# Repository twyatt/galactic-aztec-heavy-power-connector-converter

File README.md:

# About

Custom board used to convert ethernet plug to 4-pin molex connector for the [Galactic Aztec Heavy] rocket. The board was designed to interface with the [Galactic Aztec Heavy Raspberry Pi Add-on: ADC] board.

Custom EagleCAD parts on this board can be found in the [SDSU Rocket Eagle Libraries].

## Wiring
The ethernet port adheres to the following [T-568B] wiring configuration:

| Pin | Color        | Function       |
|:---:|:------------:|:--------------:|
| 1   | Orange/White |                |
| 2   | Orange       |                |
| 3   | Green/White  |                |
| 4   | Blue         | Supply Voltage |
| 5   | Blue/White   | Supply Voltage |
| 6   | Green        |                |
| 7   | Brown/White  | Ground         |
| 8   | Brown        | Ground         |

# Bill of Materials
| Qty | Name | Description                          | Part Number       | Vendor   |
|:---:|:----:|--------------------------------------|------------------:|----------|
| 1   |      | Jack RJ45 CAT5/CAT5e                 | [380-1046-ND]     | DigiKey  |
| 1   |      | Molex Mini Fit Jr. 4-pos Right Angle | [WM1352-ND]       | DigiKey  |
| 1   | D1   | LED Yellow Vf=1.8V If=2mA 0603       | [475-1196-1-ND]   | DigiKey  |
| 1   | R1   | Resistor 15kΩ 1/4W ±1% 0603          | [RHM15.0KADCT-ND] | DigiKey  |

[Galactic Aztec Heavy]: http://rocket.sdsu.edu/rockets#galactic-aztec-heavy
[Galactic Aztec Heavy Raspberry Pi Add-on: ADC]: https://github.com/twyatt/galactic-aztec-heavy-rpi-addon-adc
[SDSU Rocket Eagle Libraries]: https://github.com/twyatt/SDSURocket-Eagle-Libraries
[T-568B]: https://en.wikipedia.org/wiki/TIA/EIA-568#Wiring
[380-1046-ND]: http://www.digikey.com/product-detail/en/SS-7188-NF/380-1046-ND/388308
[WM1352-ND]: http://www.digikey.com/product-detail/en/0039301040/WM1352-ND/561079
[475-1196-1-ND]: http://www.digikey.com/product-detail/en/LY%20L29K-H1K2-26-Z/475-1196-1-ND/810357
[RHM15.0KADCT-ND]: http://www.digikey.com/product-detail/en/rohm-semiconductor/ESR03EZPF1502/RHM15.0KADCT-ND/1983758

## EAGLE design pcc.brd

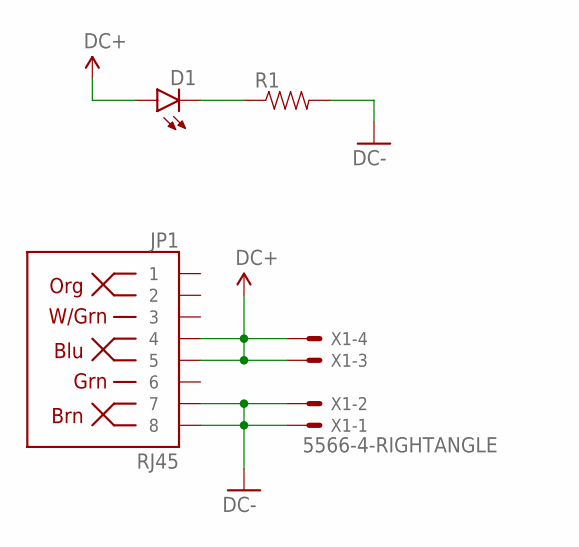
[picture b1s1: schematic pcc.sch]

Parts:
D1: LED0603; LED-0603
JP1: RJ45; RJ45-8
R1: RESISTOR0603-RES; 0603-RES
X1: 5566-4-RIGHTANGLE; 5566-4

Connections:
DC+: D1.A, JP1.4, JP1.5, X1.3, X1.4
DC-: JP1.7, JP1.8, R1.2, X1.1, X1.2
unnamed: D1.C, R1.1

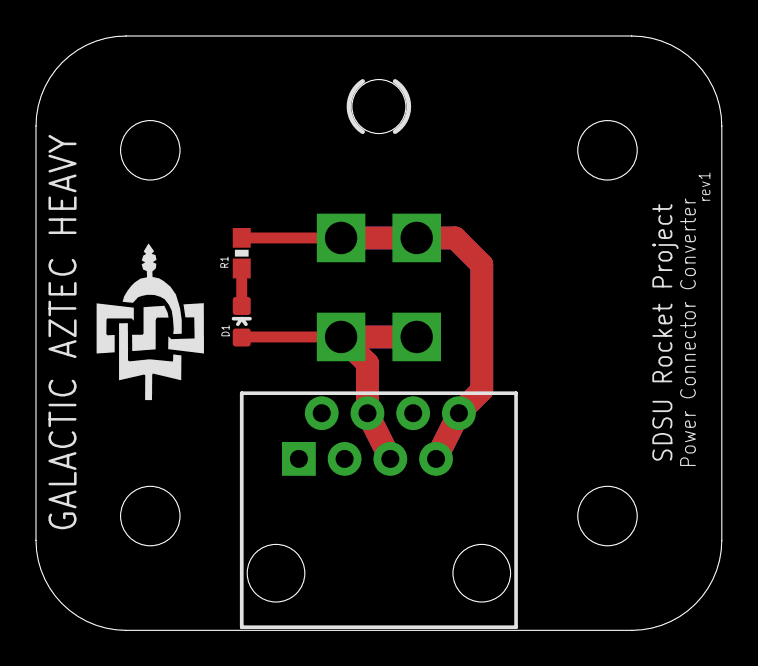
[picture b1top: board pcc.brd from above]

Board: 2 copper layers, 38.1 x 33.0 mm, 8 parts (0 on the bottom side), 3 nets.

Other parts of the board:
U$1, U$2, U$3, U$4: STAND-OFF

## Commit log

2016-03-03 Initial commit
    Designed basic ethernet-to-molex power connector converter board.
2016-03-03 Miter corners
2016-03-03 Add readme file and board images
2016-03-03 Add image of board dimensions

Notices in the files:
parts and their libraries:
SparkFun-Connectors: Licensing: Creative Commons ShareAlike 4.0 International - https://creativecommons.org/licenses/by-sa/4.0
